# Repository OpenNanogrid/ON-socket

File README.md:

# ON-socket
Drafts for a smart Extra Low Voltage Direct Current (ELVDC) socket.

## Components

### Voltage Reference

Needed for precise ADC measurements. 2.56V?

### Switching

1. n-channel MOSFET switching the negative rail, while a common conductor is tied to the positive rail and possibly earth grounded. This will reduce the overhead for gate drivers, charge pumps or p-channel mosfets as switches. What are the downsides to this approach? Voltage sensing will be difficult as the MCU and ADC will be tied at the low side, not floating. A differential sensing with a common voltage higher than the maximum bus voltage is needed.

2. p-channel MOSFET on positive rail. More expensive, Rds worse, but common GND at 0V.

Potential MOSFETs:

	n-Channel
	Name, Rds, Vds, Remark/Price
    IRFS7530-7PPbF, 1.15 mOhm, 60V
    FDMT80060DC, 1.1 mOhm Rds, 60V
    NTMFS5C604NLT1G, 1.2 mOhm, 60V
    NTMFS5C612NLT1G, 1.5 mOhm, 60V, $1.30
    IRLS3036-7PPbF, 1.5 mOhm, 60V
    IRFS7730-7PPbF, 1.7 mOhm, 75V
	CSD18540Q5B, 2.0 mOhm, 60V
    STH315N10F7-2 2.1 mOhm, 100V
    CSD18542KTT, 4.0 mOhm, 60V
    CSD19502Q5B, 4.0 mOhm, 60V
    IRFP4310Z, 4.8 mOhm, TO-247AC
    IRF3205, 8 mOhm, TO-220, cheap
        
Potential gate drivers:

	LM5109B, external bootstrap diode, $0.60
    LM27222, low Iq but max 30V
    TPS7A6350-Q1, 10µA Iq,
    UCC27201A-Q1, 1µA Iq, 120V, $1.60 
    MIC4605

### Current Sensing

1. MOSFET Vds sensing. Only valid if the consumer is a pure current source or current sink. What happens if the gate is discharged and Vds rises to 50V? The following amp and ADC will go into saturation, this needs some more thought. High impedance line from the amp, limited with a diode (crowbar)? Possible if the input impedance is high enough. Temperature drift.

2. PCB shunt. Inexpensive. Needs calibration. Quite high real estate on the PCB. Lowest part count, bidirectional sensing no problem.

3. SMD/THT resistor. Inexpensive but rather large for a high current rating. No calibration needed.

4. Integrated hall effect sensor, e.g. Allegro ACS712. Good efficiency. High price. Sourcing and sinking will both be covered (still needs antiparallel MOSFETs though). (heavy idle: 5V supply, 10mA Iq)

ADCs with integrated amps:
INA220: 12bit Bi-Directional, Zero-Drift, Low- or High-Side, I2C Out Current/Power Monitor, max 26V bus voltage. 1mA Iq
ADS1115: 16bit 4channel 8-800sps ADC with 16x PGA, i2c, differential mode, 150µA Iq
HX711: 24bit (less than 20bit usable) i2c ADC with amplifier, commonly used in weight scales, 1.5mA Iq

### Voltage Sensing

Via high impedance voltage divider into ADC: input voltage, output voltage.

### Arc Sensing

Unplugging a consumer with an inductive load or a high current flow will result in arcing. Can this event be mitigated? How to identify arcing? The resulting plasma will be a large voltage drop right at the plug.

### Micro Controller

8bit with integrated ADC should be sufficient. ESP8266 with integrated WiFi is inexpensive but has high power demands.

### Power Supply

For logic power a low Iq buck converter. Best with synchronous rectification, few external parts.  Potential candidates: TPS54061 (0.09 mA), LM5156 (0.01 mA), LM5009A (0.5 mA), all types up to 60 Vin and about 150mA output.
If the n-channel MOSFET is switched at the high side a gate driver is needed. Power supply for the gate driver needs a separate 10V rail. An LM5007, LM5010 (or an alternative with integrated synchronous rectification and enable input) can be used to form a step down converter to 10V. This step down converter should be shut down with a GPIO pin from the MCU if no load is present, so it needs an enable input.
Although a driver might charge and discharge the FET gate with 1..2A, the charge time is sufficiently low and can be buffered by caps. For a very low switching frequency (ie. using the FET as a power switch) this is fine. When the FET is used to throttle the output (e.g. via BAM / bit ampltitude modulation), the gate driver needs more power.

### Communication

Wireless: NRF24L01+ or WiFi with ESP8266
However, everything should be passive first and work plug and play without having a communication channel. 

### Optional Display

Small OLED

## Faults and Errors

1. Overload: Hiccup pattern with recovery time depending on input voltage drop.
1. Short Circuit: Switch output off. Probe current for 1ms every 500ms. Activate output again if current is below threshhold. Needs a more sophisticated algorithm for plug-in events when input capacitors are charged, soft start could be implemented with PWM.
1. Polyfuse? 
1. Diode over output against back-EMF.

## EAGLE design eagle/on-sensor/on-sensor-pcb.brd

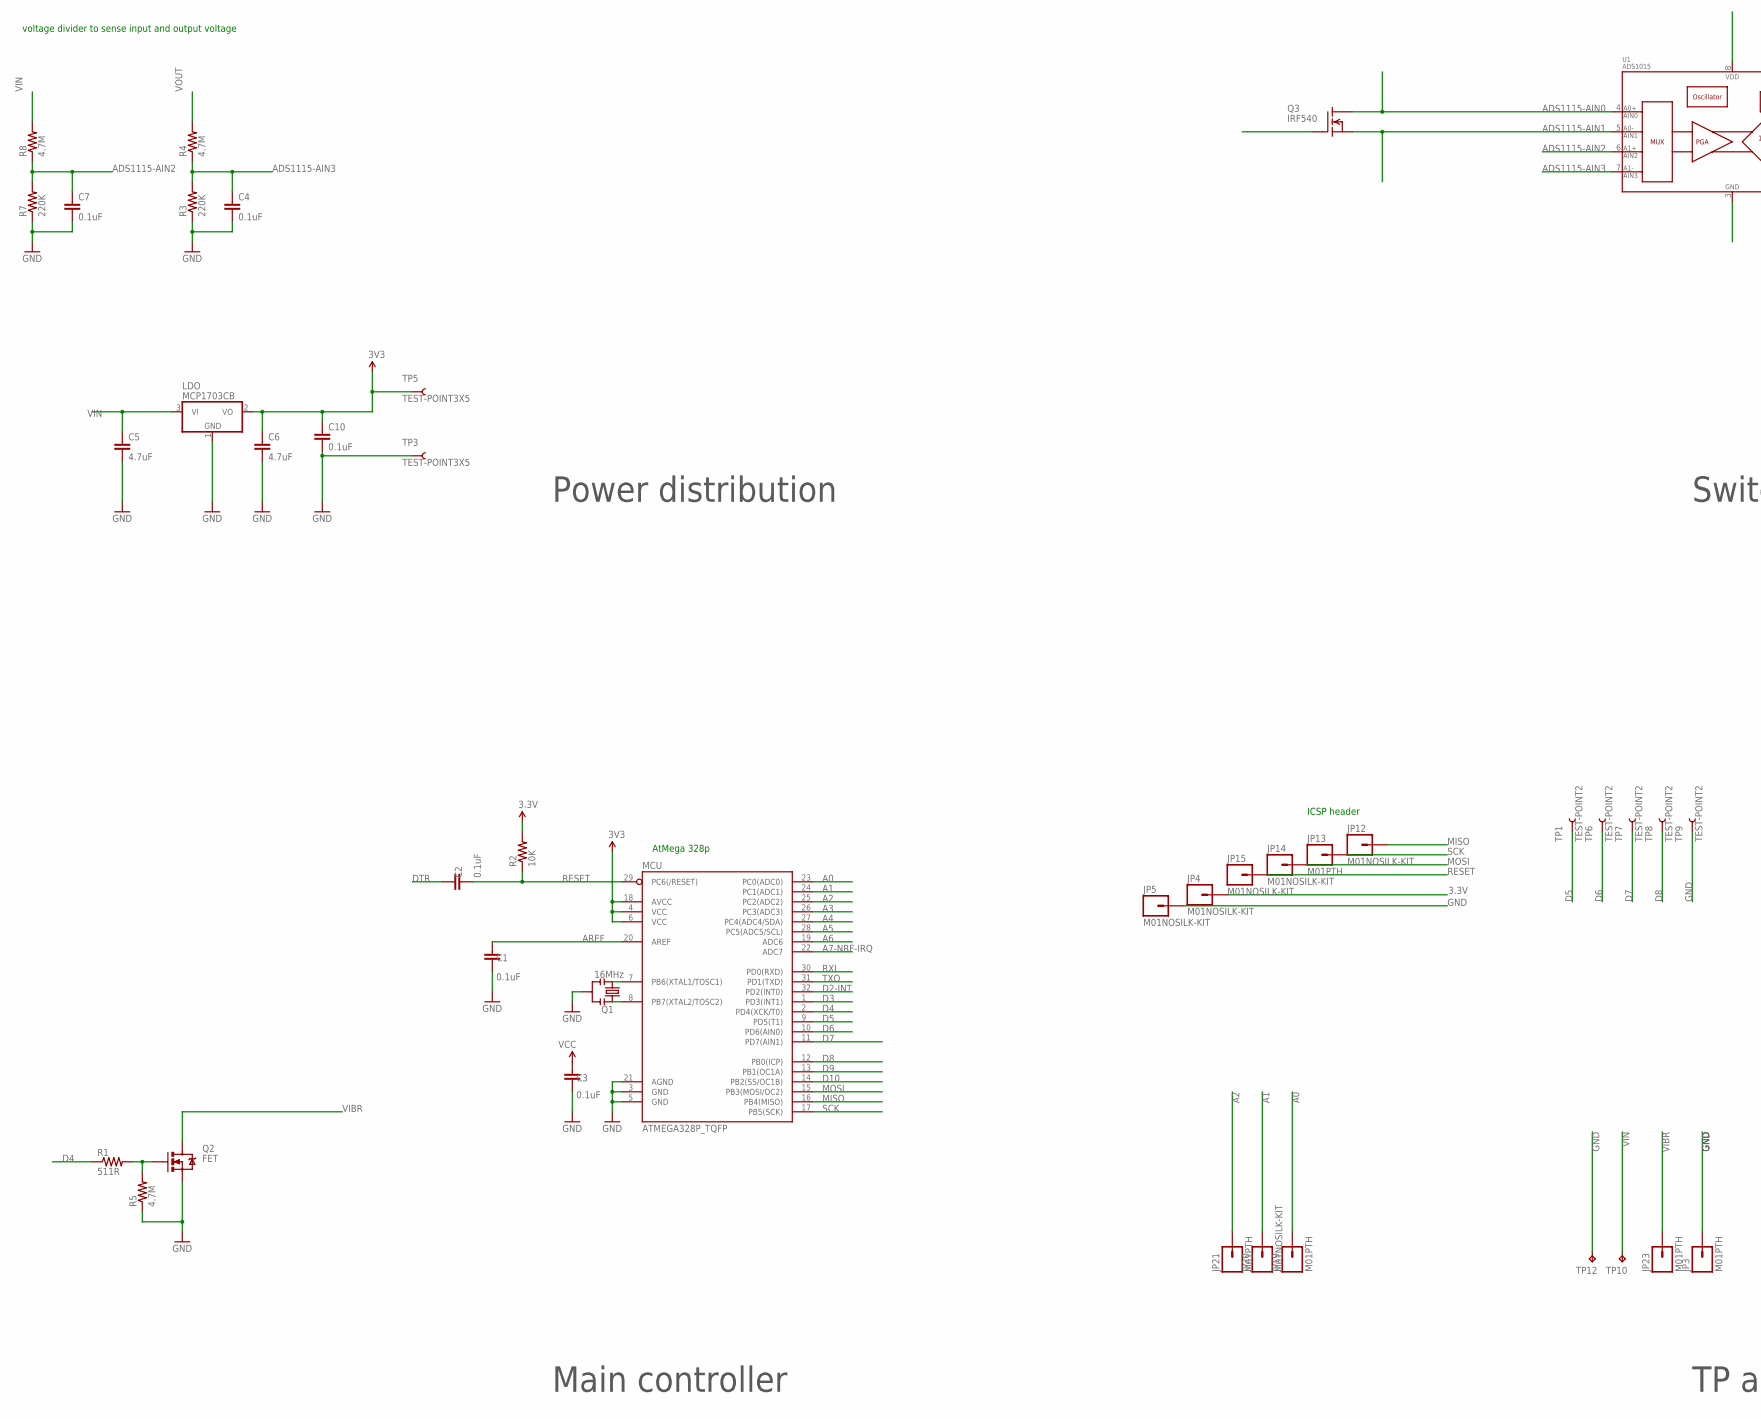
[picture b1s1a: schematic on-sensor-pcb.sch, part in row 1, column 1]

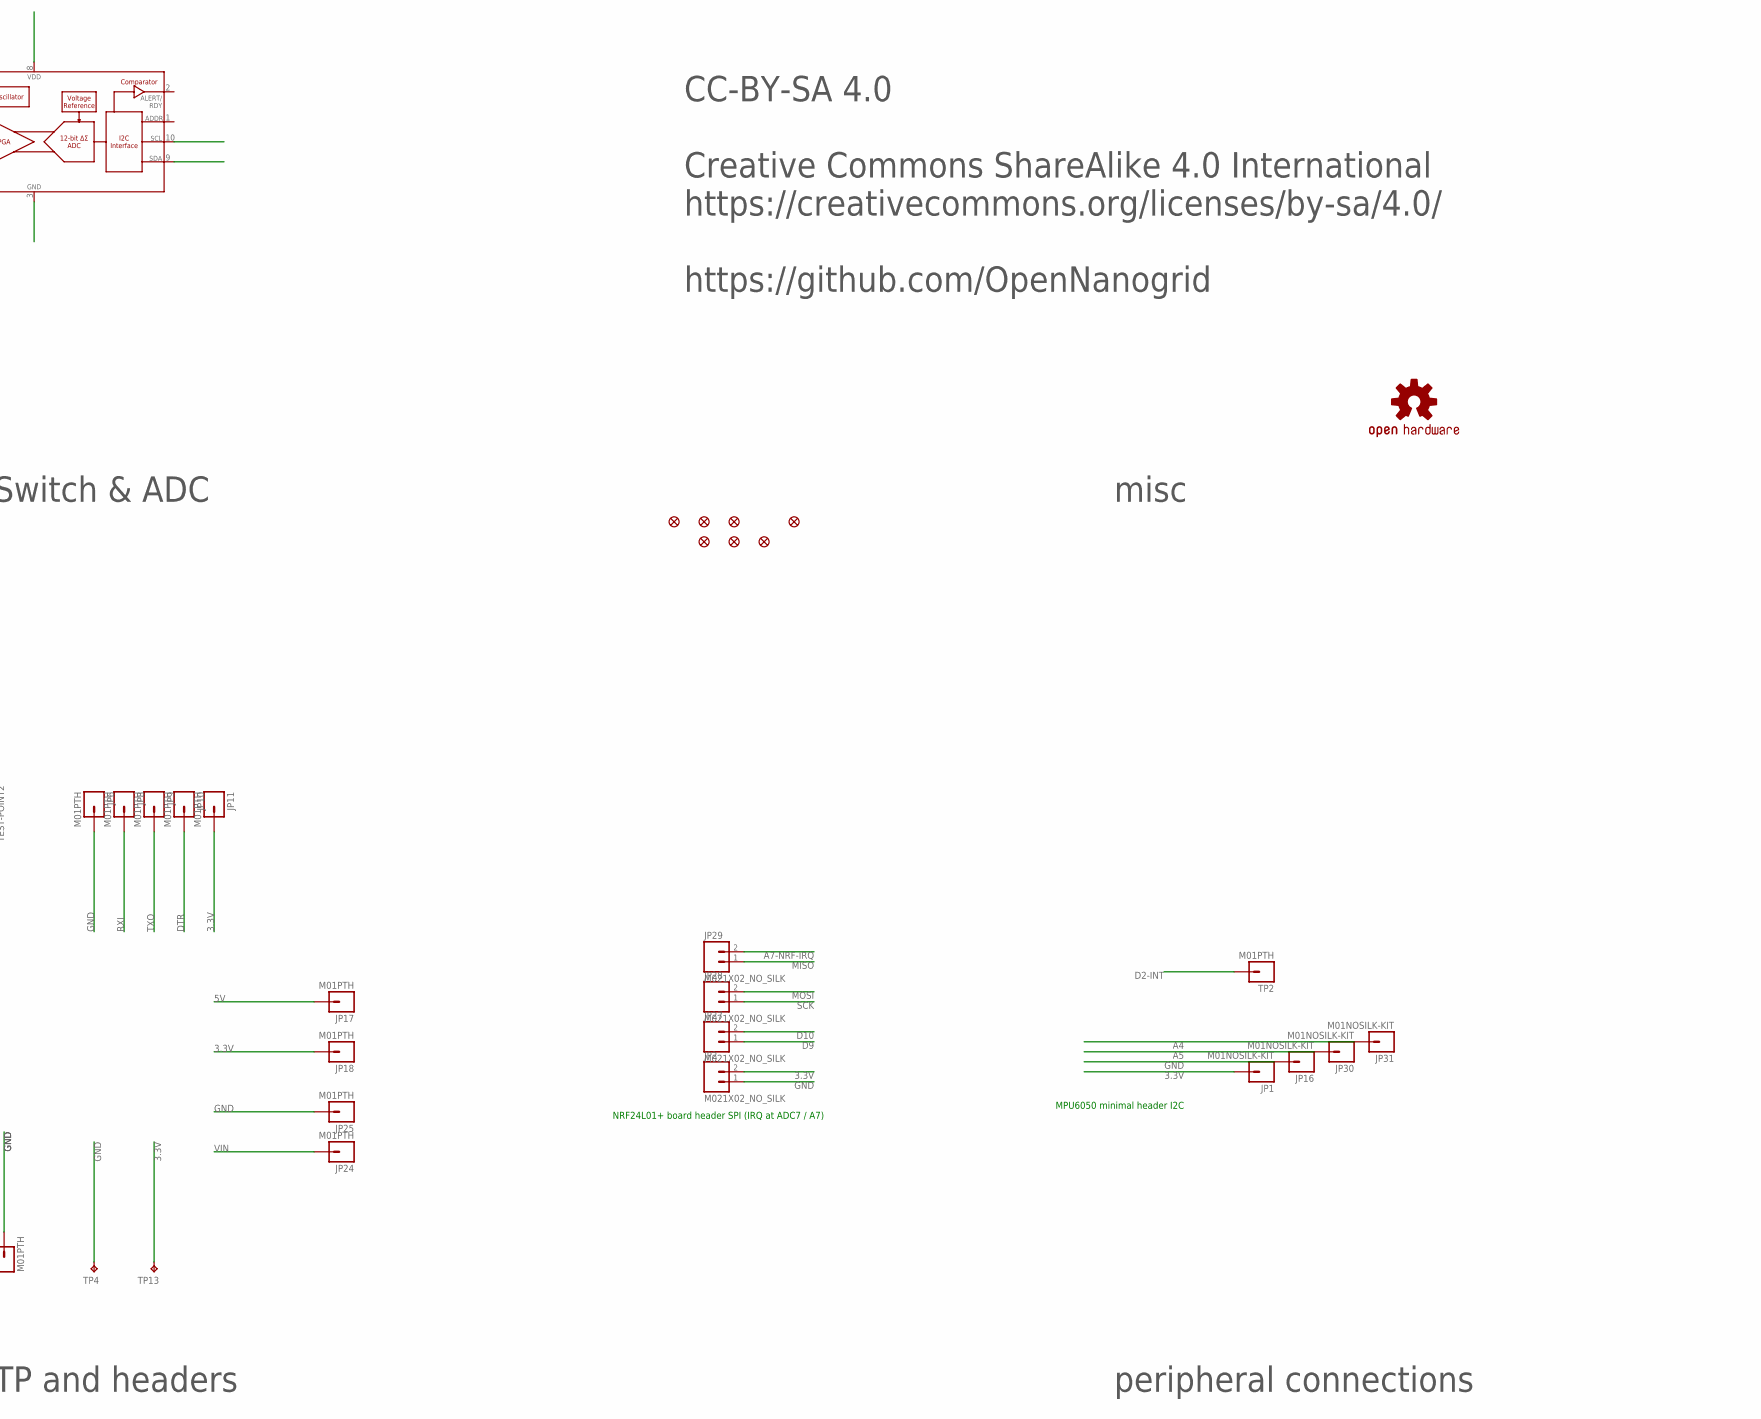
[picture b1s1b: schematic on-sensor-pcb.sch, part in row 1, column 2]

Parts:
C1, C2, C3, C4, C7: 0.1uF; C0402K
C5, C6: 4.7uF; 0603-CAP
C10: 0.1uF; C0603
FID1, FID2, FID3, FID5, FID7, FID8, FID9: FIDUCIALUFIDUCIAL; MICRO-FIDUCIAL
JP1, JP4, JP5, JP12, JP14, JP15, JP16, JP20, JP30, JP31: M01NOSILK-KIT; 1X01NS-KIT
JP2, JP27, JP28, JP29: M021X02_NO_SILK; 1X02_NO_SILK
JP3, JP6, JP8, JP9, JP10, JP11, JP13, JP17, JP18, JP19, JP21, JP23, JP24, JP25: M01PTH; 1X01
LDO: MCP1703CB; SOT23
LOGO1: OSHW-LOGOS; OSHW-LOGO-S
MCU: ATMEGA328P_TQFP; TQFP32-08
Q1: 16MHz; RESONATOR-SMD
Q2: FET; SOT23-3
Q3: IRF540; TO220
R1: 511R; 0603-RES
R2: 10K; 0603-RES
R3, R7: 220K; 0603-RES
R4, R5, R8: 4.7M; 0603-RES
TP1, TP6, TP7, TP8, TP9: TEST-POINT2; PAD.02X.02
TP2: M01PTH; 1X01
TP3, TP5: TEST-POINT3X5; PAD.03X.05
TP4, TP10, TP12, TP13: TPTP20R; TP20R
U1: ADS1015; MSOP10

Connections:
3.3V: C3.2, C6.1, C10.1, JP1.1, JP2.2, JP4.1, JP11.1, JP18.1, LDO.2 (VO), MCU.4 (VCC), MCU.6 (VCC), MCU.18 (AVCC), R2.2, TP5.P$1, TP13.TP
5V: JP17.1
A0: JP19.1, MCU.23 (PC0(ADC0))
A1: JP20.1, MCU.24 (PC1(ADC1))
A2: JP21.1, MCU.25 (PC2(ADC2))
A3: MCU.26 (PC3(ADC3))
A4: JP31.1, MCU.27 (PC4(ADC4/SDA))
A5: JP30.1, MCU.28 (PC5(ADC5/SCL))
A6: MCU.19 (ADC6)
A7-NRF-IRQ: JP29.2, MCU.22 (ADC7)
ADS1115-AIN0: Q3.2 (D), U1.4 (AIN0)
ADS1115-AIN1: Q3.3 (S), U1.5 (AIN1)
ADS1115-AIN2: C7.1, R7.2, R8.1, U1.6 (AIN2)
ADS1115-AIN3: C4.1, R3.2, R4.1, U1.7 (AIN3)
AREF: C1.2, MCU.20 (AREF)
D2-INT: MCU.32 (PD2(INT0)), TP2.1
D3: MCU.1 (PD3(INT1))
D4: MCU.2 (PD4(XCK/T0)), R1.1
D5: MCU.9 (PD5(T1)), TP1.P$1
D6: MCU.10 (PD6(AIN0)), TP6.P$1
D7: MCU.11 (PD7(AIN1)), TP7.P$1
D8: MCU.12 (PB0(ICP)), TP8.P$1
D9: JP27.1, MCU.13 (PB1(OC1A))
D10: JP27.2, MCU.14 (PB2(SS/OC1B))
DTR: C2.2, JP10.1
GND: C1.1, C3.1, C4.2, C5.2, C6.2, C7.2, C10.2, JP2.1, JP3.1, JP5.1, JP6.1, JP16.1, JP25.1, LDO.1 (GND), MCU.3 (GND), MCU.5 (GND), MCU.21 (AGND), Q1.2, Q2.2 (S), R3.1, R5.1, R7.1, TP3.P$1, TP4.TP, TP9.P$1, TP12.TP
MISO: JP12.1, JP29.1, MCU.16 (PB4(MISO))
MOSI: JP14.1, JP28.2, MCU.15 (PB3(MOSI/OC2))
unnamed: MCU.8 (PB7(XTAL2/TOSC2)), Q1.1
unnamed: MCU.7 (PB6(XTAL1/TOSC1)), Q1.3
unnamed: Q2.1 (G), R1.2, R5.2
RESET: C2.1, JP15.1, MCU.29 (PC6(/RESET)), R2.1
RXI: JP8.1, MCU.30 (PD0(RXD))
SCK: JP13.1, JP28.1, MCU.17 (PB5(SCK))
TXO: JP9.1, MCU.31 (PD1(TXD))
VIBR: JP23.1, Q2.3 (D)
VIN: C5.1, JP24.1, LDO.3 (VI), R8.2, TP10.TP
VOUT: R4.2

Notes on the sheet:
NRF24L01+ board header SPI (IRQ at ADC7 / A7)
MPU6050 minimal header I2C
AtMega 328p
voltage divider to sense input and output voltage
ICSP header
Power distribution
Main controller
TP and headers
peripheral connections
misc
Switch & ADC
CC-BY-SA 4.0 Creative Commons ShareAlike 4.0 International https://creativecommons.org/licenses/by-sa/4.0/ https://github.com/OpenNanogrid

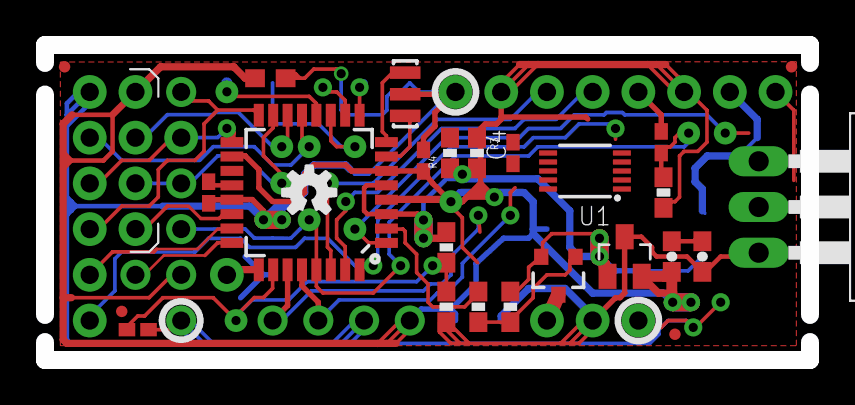
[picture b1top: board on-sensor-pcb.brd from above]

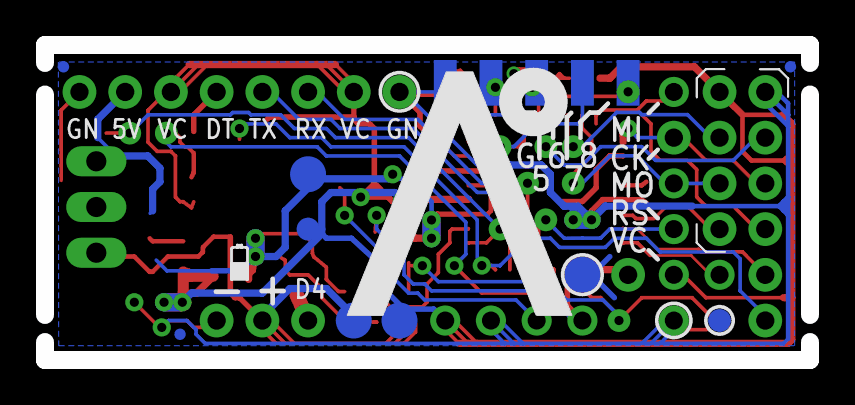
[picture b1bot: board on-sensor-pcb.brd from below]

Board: 2 copper layers, 42.5 x 17.5 mm, 69 parts (14 on the bottom side), 33 nets.

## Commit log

2016-05-18 create repo
2016-05-18 Initial thoughts about components.
2016-05-18 formatting
2016-05-19 Current sensing
2016-05-19 CAD components for wall outlet
2016-05-19 rendered CAD files
2016-05-19 Added render mockup
2016-05-21 Eagle PCB started
2016-05-21 add eagle specific temp files to gitignore
2016-05-21 remove eagle backups
2016-05-21 added debug header to one side
2016-05-22 MOSFETs
2016-05-22 Gate driver
2016-05-23 ON Con 32A Wire CAD
2016-10-19 more rendered drafts
2016-10-22 file tree update

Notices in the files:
parts and their libraries:
SparkFun-DiscreteSemi: Licensing: Creative Commons ShareAlike 4.0 International - https://creativecommons.org/licenses/by-sa/4.0
